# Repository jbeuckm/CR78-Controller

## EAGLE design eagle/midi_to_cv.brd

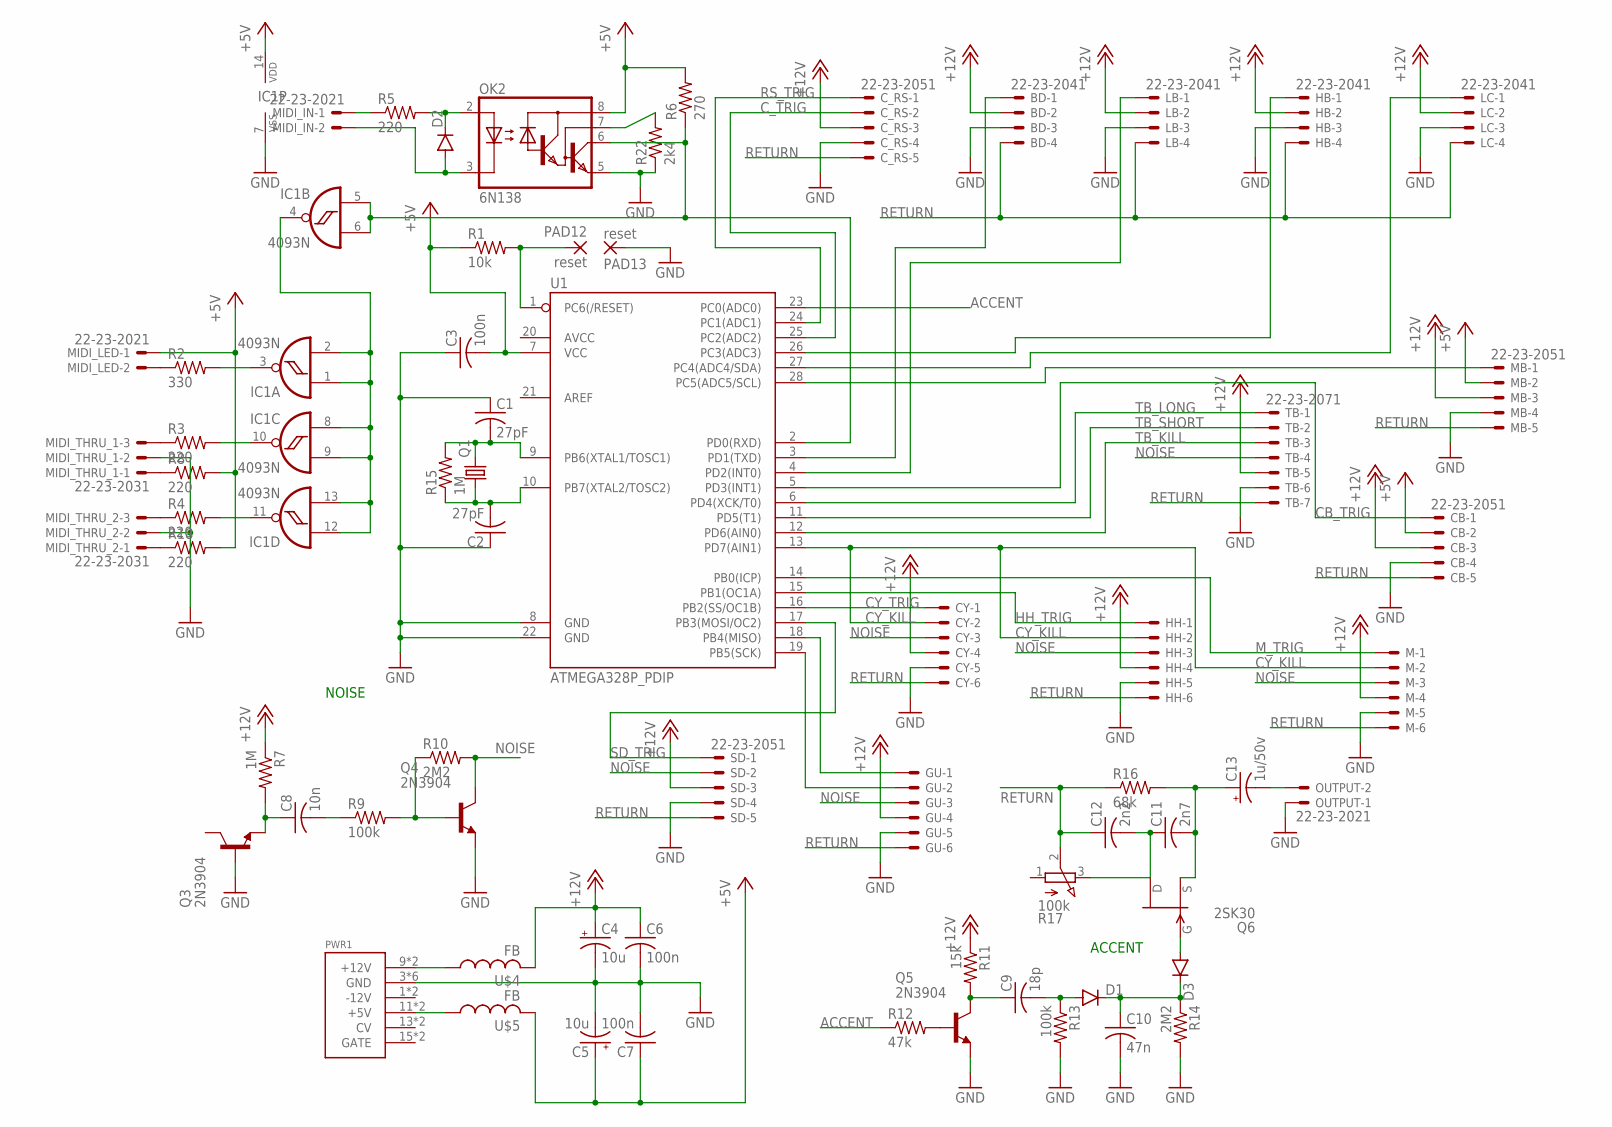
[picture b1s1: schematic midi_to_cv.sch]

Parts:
BD: 22-23-2041
C1, C2: 27pF; C025-040X050
C3: 100n; C025-040X050
C4, C5: 10u; B45181A
C6, C7: 100n; C050-024X044
C8: 10n; C025-040X050
C9: 18p; C050-025X075
C10: 47n; C025-040X050
C11: 2n7; C025-040X050
C12: 2n2; C025-040X050
C13: 1u/50v; B45181A
CB: 22-23-2051
CY: 22-23-2061
C_RS: 22-23-2051
D1: DIODEKIT; DIODE-1N4148-KIT
D2, D3: DIODE1N4148; DIODE-1N4148
GU: 22-23-2061
HB: 22-23-2041
HH: 22-23-2061
IC1: 4093N; DIL14
LB: 22-23-2041
LC: 22-23-2041
M: 22-23-2061
MB: 22-23-2051
MIDI_IN: 22-23-2021
MIDI_LED: 22-23-2021
MIDI_THRU_1, MIDI_THRU_2: 22-23-2031
OK2: 6N138; DIL08
OUTPUT: 22-23-2021
PAD12, PAD13: reset; 2,54/0,9
PWR1: POWER; POWER_16
Q1: CRYSTALHC49U-V; HC49U-V
Q3, Q4, Q5: 2N3904; TO92
Q6: 2SK30; TO92
R1: 10k; 0204/7
R2: 330; 0204/7
R3, R4, R5, R8, R18: 220; 0204/7
R6: 270; 0204/7
R7, R15: 1M; 0204/7
R9, R13: 100k; 0204/7
R10, R14: 2M2; 0204/7
R11: 15k; 0204/7
R12: 47k; 0207/12
R16: 68k; 0204/7
R17: 100k; 3RP/1610N
R22: 2k4; 0204/7
SD: 22-23-2051
TB: 22-23-2071
U1: ATMEGA328P_PDIP; DIL28-3
U$4, U$5: FB

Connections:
+5V: C3.2, C5.+, C7.1, CB.2, IC1.14 (VDD), MB.2, MIDI_LED.1, OK2.8 (VCC), R1.1, R6.2, R8.2, R18.2, U1.7 (VCC), U$5.P$2 (2)
+12V: BD.2, C4.+, C6.1, CB.3, CY.4, C_RS.3, GU.4, HB.2, HH.4, LB.2, LC.2, M.4, MB.3, R7.1, R11.1, SD.3, TB.5, U$4.P$2 (2)
ACCENT: R12.1, U1.23 (PC0(ADC0))
CB_TRIG: CB.1, U1.5 (PD3(INT1))
CY_KILL: CY.2, HH.2, M.2, U1.13 (PD7(AIN1))
CY_TRIG: CY.1, U1.16 (PB2(SS/OC1B))
C_TRIG: C_RS.2, U1.25 (PC2(ADC2))
GND: BD.3, C1.1, C2.1, C3.1, C4.-, C5.-, C6.2, C7.2, C10.2, CB.4, CY.5, C_RS.4, GU.5, HB.3, HH.5, IC1.7 (VSS), LB.3, LC.3, M.5, MB.4, MIDI_THRU_1.2, MIDI_THRU_2.2, OK2.5 (GND), OUTPUT.1, PAD13.1, PWR1.3 (GND), PWR1.4 (GND), PWR1.5 (GND), PWR1.6 (GND), PWR1.7 (GND), PWR1.8 (GND), Q3.2 (B), Q4.3 (E), Q5.3 (E), R13.2, R14.2, R22.1, SD.4, TB.6, U1.8 (GND), U1.22 (GND)
HH_TRIG: HH.1, U1.15 (PB1(OC1A))
M_TRIG: M.1, U1.14 (PB0(ICP))
unnamed: PAD12.1, R1.2, U1.1 (PC6(/RESET))
unnamed: PWR1.9 (+12V), PWR1.10 (+12V), U$4.P$1 (1)
unnamed: BD.1, U1.3 (PD1(TXD))
unnamed: C1.2, Q1.2, R15.2, U1.9 (PB6(XTAL1/TOSC1))
unnamed: C2.2, Q1.1, R15.1, U1.10 (PB7(XTAL2/TOSC2))
unnamed: C8.1, Q3.3 (E), R7.2
unnamed: LB.1, U1.4 (PD2(INT0))
unnamed: C8.2, R9.1
unnamed: GU.1, U1.18 (PB4(MISO))
unnamed: GU.2, U1.19 (PB5(SCK))
unnamed: IC1.5 (I0), IC1.6 (I1), OK2.6 (VO), R6.1, U1.2 (PD0(RXD))
unnamed: IC1.3 (O), R2.2
unnamed: Q4.2 (B), R9.2, R10.1
unnamed: HB.1, U1.26 (PC3(ADC3))
unnamed: C9.1, Q5.1 (C), R11.2
unnamed: Q5.2 (B), R12.2
unnamed: D2.A, MIDI_IN.2, OK2.3 (C)
unnamed: D2.C, OK2.2 (A), R5.2
unnamed: MIDI_IN.1, R5.1
unnamed: MIDI_THRU_1.1, R8.1
unnamed: C9.2, D1.A, R13.1
unnamed: C10.1, D1.C, D3.C, R14.1
unnamed: D3.A, Q6.2 (G)
unnamed: MB.1, U1.28 (PC5(ADC5/SCL))
unnamed: LC.1, U1.27 (PC4(ADC4/SDA))
unnamed: C13.-, OUTPUT.2
unnamed: IC1.10 (O), R3.2
unnamed: IC1.11 (O), R4.2
unnamed: C11.1, C12.2, Q6.1 (D), R17.3 (E)
unnamed: IC1.1 (I0), IC1.2 (I1), IC1.4 (O), IC1.8 (I0), IC1.9 (I1), IC1.12 (I0), IC1.13 (I1)
unnamed: MIDI_LED.2, R2.1
unnamed: C11.2, C13.+, Q6.3 (S), R16.2
unnamed: MIDI_THRU_1.3, R3.1
unnamed: MIDI_THRU_2.3, R4.1
unnamed: MIDI_THRU_2.1, R18.1
unnamed: OK2.7 (VB), R22.2
unnamed: PWR1.11 (+5V), PWR1.12 (+5V), U$5.P$1 (1)
NOISE: CY.3, GU.3, HH.3, M.3, Q4.1 (C), R10.2, SD.2, TB.4
RETURN: BD.4, C12.1, CB.5, CY.6, C_RS.5, GU.6, HB.4, HH.6, LB.4, LC.4, M.6, MB.5, R16.1, R17.2 (S), SD.5, TB.7
RS_TRIG: C_RS.1, U1.24 (PC1(ADC1))
SD_TRIG: SD.1, U1.17 (PB3(MOSI/OC2))
TB_KILL: TB.3, U1.12 (PD6(AIN0))
TB_LONG: TB.1, U1.6 (PD4(XCK/T0))
TB_SHORT: TB.2, U1.11 (PD5(T1))

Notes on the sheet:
NOISE
ACCENT

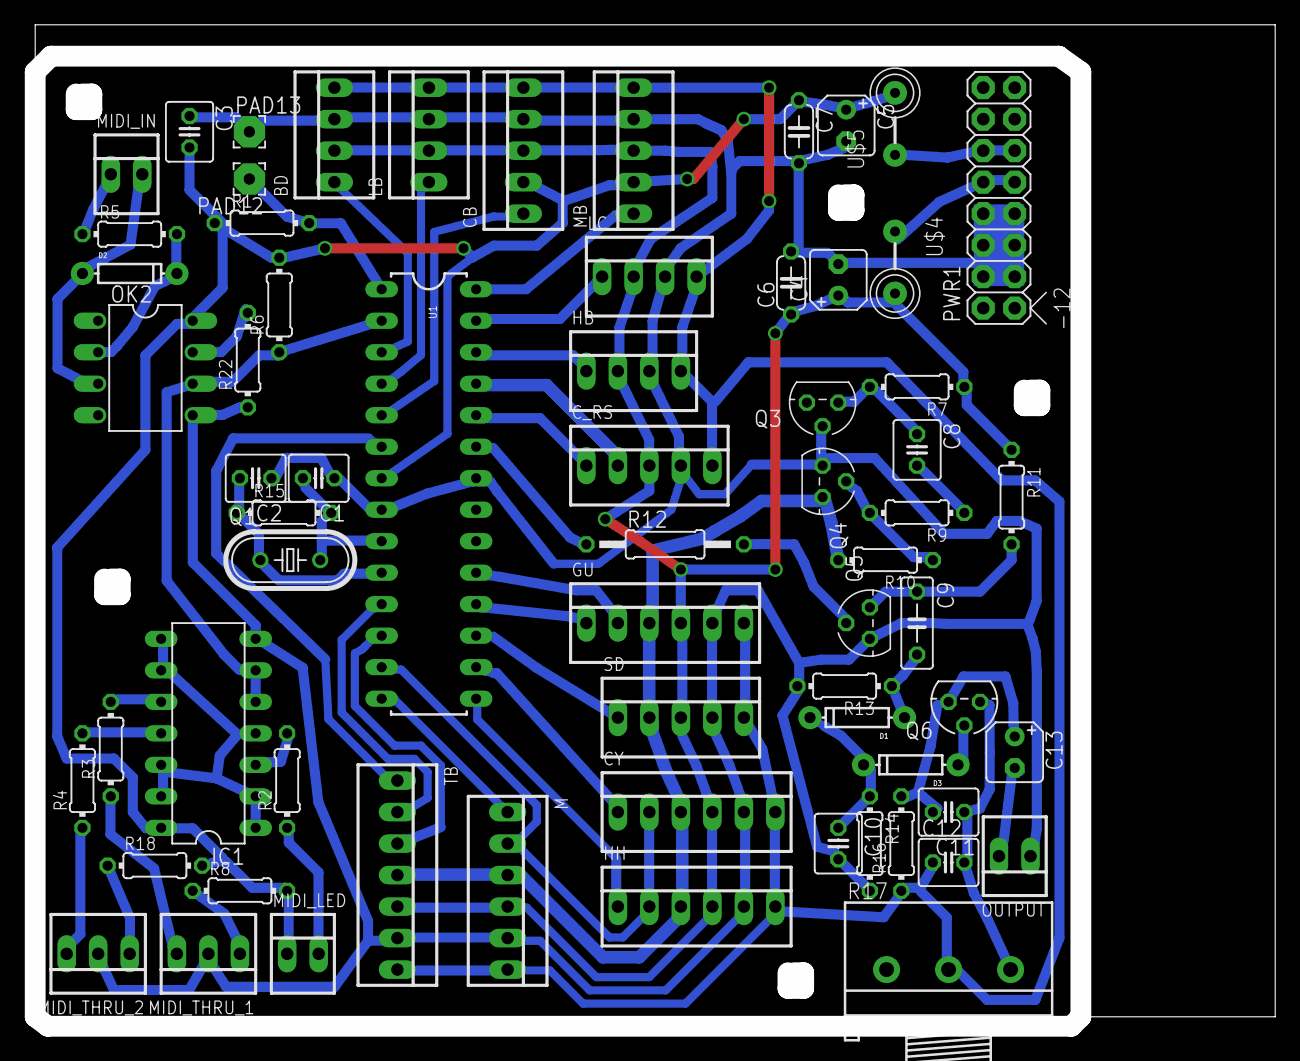
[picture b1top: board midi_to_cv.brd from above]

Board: 2 copper layers, 99.2 x 79.9 mm, 66 parts (0 on the bottom side), 54 nets.

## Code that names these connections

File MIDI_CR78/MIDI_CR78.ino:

#include <MIDI.h>
#include <SoftwareSerialIn.h>

#define BD_PIN 1
#define SD_PIN 11
#define LB_PIN 2
#define HB_PIN A3
#define LC_PIN A4
#define RS_PIN A1
#define C_PIN A2
#define CB_PIN 3
#define TB_SHORT_PIN 5
#define TB_LONG_PIN 4
#define TB_KILL_PIN 6
#define MB_PIN A5

#define GU_STOP_PIN 12
#define GU_SLOW_PIN 13

#define CY_PIN 10
#define HH_PIN 9
#define M_PIN 8
#define CY_KILL_PIN 7

#define ACCENT_PIN A0

#define REGULAR_PIN_COUNT 14

#define BASE_MIDI_NOTE 60

byte voice_map[] = {BD_PIN, SD_PIN, LB_PIN, HB_PIN, 
                  LC_PIN, RS_PIN, C_PIN, CB_PIN, 
                  TB_SHORT_PIN, TB_LONG_PIN, 
                  MB_PIN, M_PIN, HH_PIN, CY_PIN};

byte voice_gates[] = {0, 0, 0, 0,
                    0, 0, 0, 0,
                    0, 0, 0, 0,
                    0, 0};

SoftwareSerialIn serialIn(0);
MIDI_CREATE_INSTANCE(SoftwareSerialIn, serialIn, midiIn);



void handleNoteOn(byte channel, byte pitch, byte velocity)
{
  byte voice = pitch - BASE_MIDI_NOTE;

  if (voice >= 0 && voice < REGULAR_PIN_COUNT) { 
  
    if (velocity >= 100) {
      digitalWrite(ACCENT_PIN, HIGH);
    } else {
      digitalWrite(ACCENT_PIN, LOW);
    }
    
    byte voice_pin = voice_map[voice];
  
    switch (voice_pin) {
      
      case TB_SHORT_PIN:
      case TB_LONG_PIN:
        digitalWrite(TB_KILL_PIN, HIGH);
        break;
  
      case CY_PIN:
      case HH_PIN:
      case M_PIN:
        digitalWrite(CY_KILL_PIN, LOW);
        break;
    }

    voice_gates[voice] = 8;
  }

  else if (voice == REGULAR_PIN_COUNT) {
    digitalWrite(GU_SLOW_PIN, LOW);
    digitalWrite(GU_STOP_PIN, LOW);
  }
  else if (voice == REGULAR_PIN_COUNT + 1) {
    digitalWrite(GU_SLOW_PIN, HIGH);
    digitalWrite(GU_STOP_PIN, LOW);
  }
}

void handleNoteOff(byte channel, byte pitch, byte velocity)
{
  byte voice = pitch - 60;

  if (voice >= 0 && voice < REGULAR_PIN_COUNT) { 
    
    byte voice_pin = voice_map[voice];
  
    switch (voice_pin) {
      
      case TB_SHORT_PIN:
      case TB_LONG_PIN:
        digitalWrite(TB_KILL_PIN, LOW);
        break;
  
      case CY_PIN:
      case HH_PIN:
      case M_PIN:
        digitalWrite(CY_KILL_PIN, HIGH);
        break;
    }
  }
  
  else if (voice == REGULAR_PIN_COUNT || voice == REGULAR_PIN_COUNT + 1) {
    digitalWrite(GU_STOP_PIN, HIGH);
  }
}


int i;

ISR(TIMER1_COMPA_vect) {

  for (i=0; i<REGULAR_PIN_COUNT; i++) {
    byte voice_pin = voice_map[i];
    if (voice_gates[i] > 1) {
      digitalWrite(voice_pin, HIGH);
      voice_gates[i] -= 1;
    } else if (voice_gates[i] == 1) {
      digitalWrite(voice_pin, LOW);
      voice_gates[i] = 0;
    }    
  }   
 
}


// -----------------------------------------------------------------------------

void setup()
{
  int j;
  for (j = 0; j < REGULAR_PIN_COUNT; j++) {
    pinMode(voice_map[j], OUTPUT);
    digitalWrite(voice_map[j], LOW);
  }

  pinMode(CY_KILL_PIN, OUTPUT);
  digitalWrite(CY_KILL_PIN, HIGH);
  
  pinMode(TB_KILL_PIN, OUTPUT);
  digitalWrite(TB_KILL_PIN, HIGH);
  
  pinMode(ACCENT_PIN, OUTPUT);
  digitalWrite(ACCENT_PIN, LOW);

  pinMode(GU_STOP_PIN, OUTPUT);
  pinMode(GU_SLOW_PIN, OUTPUT);
  digitalWrite(GU_STOP_PIN, HIGH);

  midiIn.setHandleNoteOn(handleNoteOn);
  midiIn.setHandleNoteOff(handleNoteOff);

  cli();//stop interrupts
  
  //set timer1 interrupt at 1kHz
  TCCR1A = 0;// set entire TCCR1A register to 0
  TCCR1B = 0;// same for TCCR1B
  TCNT1  = 0;//initialize counter value to 0;
  // set timer count for 1khz increments
  OCR1A = 1999;// = (16*10^6) / (1000*8) - 1
  // turn on CTC mode
  TCCR1B |= (1 << WGM12);
  // Set CS11 bit for 8 prescaler
  TCCR1B |= (1 << CS11);   
  // enable timer compare interrupt
  TIMSK1 |= (1 << OCIE1A);
  
  sei();//allow interrupts
    
    
  midiIn.begin(10);
  midiIn.turnThruOff();
}

void loop()
{
  midiIn.read();
}

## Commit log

2016-05-25 basic midi atmega circuit
2016-05-25 cleaned out old code libraries for DACs
2016-05-25 noise and accent and raw gates
2016-06-06 connectors for each voice
2016-06-07 close to routed
2016-06-07 95pct auto
2016-06-07 added midi led and thru
2016-06-07 shifted accent pin closer to circuit
2016-06-08 tweaks toward auto
2016-06-08 96pct auto
2016-06-08 97pct auto
2016-06-09 routed
2016-06-09 tweaks
2016-06-11 arduino code compiles
2016-06-11 bd not working, others seem fine
2016-06-19 custom gate and freq code for guiro working now
2016-06-24 using a simplified softwareserial with in only
2016-10-23 SoftwareSerialIn as included library and accent depends on velocity

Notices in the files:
parts and their libraries:
SparkFun-DiscreteSemi: Licensing: Creative Commons ShareAlike 4.0 International - https://creativecommons.org/licenses/by-sa/4.0
